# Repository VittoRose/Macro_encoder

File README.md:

# HID Encoder with Arduino IDE and RP2040 Zero
## Overview
This project provides the firmware and hardware designs for creating a Human Interface Device (HID) Encoder using the RP2040 Zero microcontroller and Arduino IDE. The encoder can be utilized in various applications such as custom keyboards, MIDI controllers, or any other device that requires an encoder input.

## Repository Contents
* Firmware: Source code written in C++ for the Arduino IDE, tailored for the RP2040 Zero.
* Hardware Schematics: Detailed circuit diagrams and PCB layouts for fabricating the encoder hardware.
* 3D Models: STL files for 3D printing the enclosure and other mechanical components of the encoder.
## Features
**pass**
## Getting Started
### Prerequisites
* Arduino IDE: Ensure you have the latest version installed.
* RP2040 Board Support: Add the RP2040 board package to your Arduino IDE. Follow the instructions on the Arduino official website.
* Required Libraries: Install any additional libraries as specified in the libraries.txt file included in the repository.
### Hardware
* PCB Fabrication: Use the provided schematics and PCB layout files to fabricate your printed circuit board.
* Components: Gather all required electronic components
    - 1x RP2040 Zero
    - 1x Encoder with switch
    - 2x 15 ohm resistor, 1x 45 ohm resistor
    - 1x RGB LED tht

* Assembly: Solder the components onto the PCB as per the schematics.
### Software
Upload Macro_encoder.ino to your RP2040

### 3D Printing
* Download STL Files: Navigate to the 3d_models directory in the repository.
* Print Enclosure: Use a 3D printer to print the provided STL files for the enclosure.
* Assembly: Assemble the printed parts to house the PCB and secure the encoder.
### Usage
 This device should be plug and play on any windows machine.

### Schematics and 3D Models
The **PCB schematics directory** contains all necessary files for PCB design and manufacturing.
The **3D model** directory includes STL files for 3D printing the encoder housing and related components.
Contributing

I presonally welcome contributions! If you have suggestions or improvements, please fork the repository and create a pull request.

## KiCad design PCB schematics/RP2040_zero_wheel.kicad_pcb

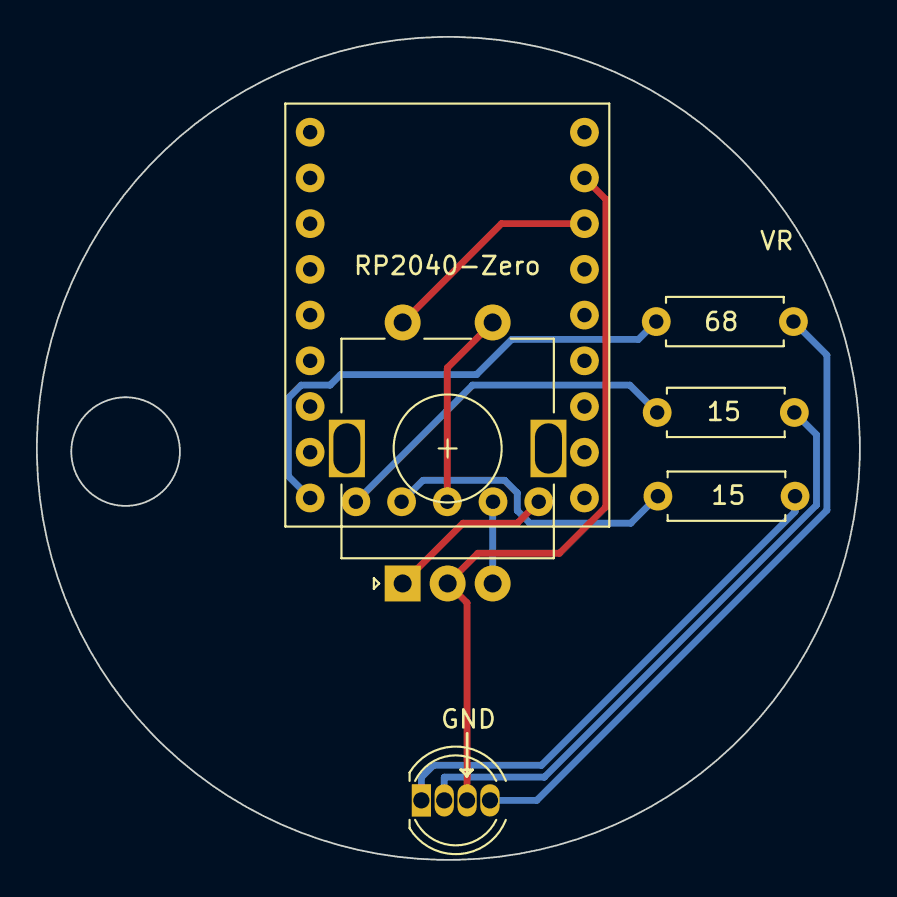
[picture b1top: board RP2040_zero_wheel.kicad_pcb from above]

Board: 2 copper layers, 45.7 x 45.7 mm, 6 parts (0 on the bottom side), 11 nets.

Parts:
15, 15#2, 68: R; R_Axial_DIN0207_L6.3mm_D2.5mm_P7.62mm_Horizontal
D1: LED_BGKR; LED_D5.0mm-4_RGB
RP2040-Zero: RP2040-Zero
SW1: RotaryEncoder_Switch; RotaryEncoder_Alps_EC11E-Switch_Vertical_H20mm

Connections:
3.3V: RP2040-Zero.3 (3V3), SW1.S2
GND: D1.3 (K), RP2040-Zero.2 (GND), SW1.C
unnamed: 15.1, D1.1 (BA)
unnamed: 15#2.2, D1.2 (GA)
unnamed: 68.2, D1.4 (RA)
unnamed: RP2040-Zero.10 (GP0), SW1.A
unnamed: RP2040-Zero.11 (GP1), SW1.B
unnamed: RP2040-Zero.12 (GP2), SW1.S1
unnamed: 15.2, RP2040-Zero.13 (GP3)
unnamed: 15#2.1, RP2040-Zero.14 (GP4)
unnamed: 68.1, RP2040-Zero.15 (GP5)

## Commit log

2024-06-25 Windows navigation complete
2024-06-25 Double click to change state
2024-06-30 Fixed alt_tab, added arrow mode
2024-08-01 Probelms with encoder motion
2024-08-01 Improved code
2024-08-01 Almost work (2_Loops)
2024-08-01 Update Tab_alt and Coursor
2024-08-01 State transition fix
2024-08-01 Reduced LED brightness Added vertical cursor
2024-08-01 PCB upload
2024-08-01 3D model upload
